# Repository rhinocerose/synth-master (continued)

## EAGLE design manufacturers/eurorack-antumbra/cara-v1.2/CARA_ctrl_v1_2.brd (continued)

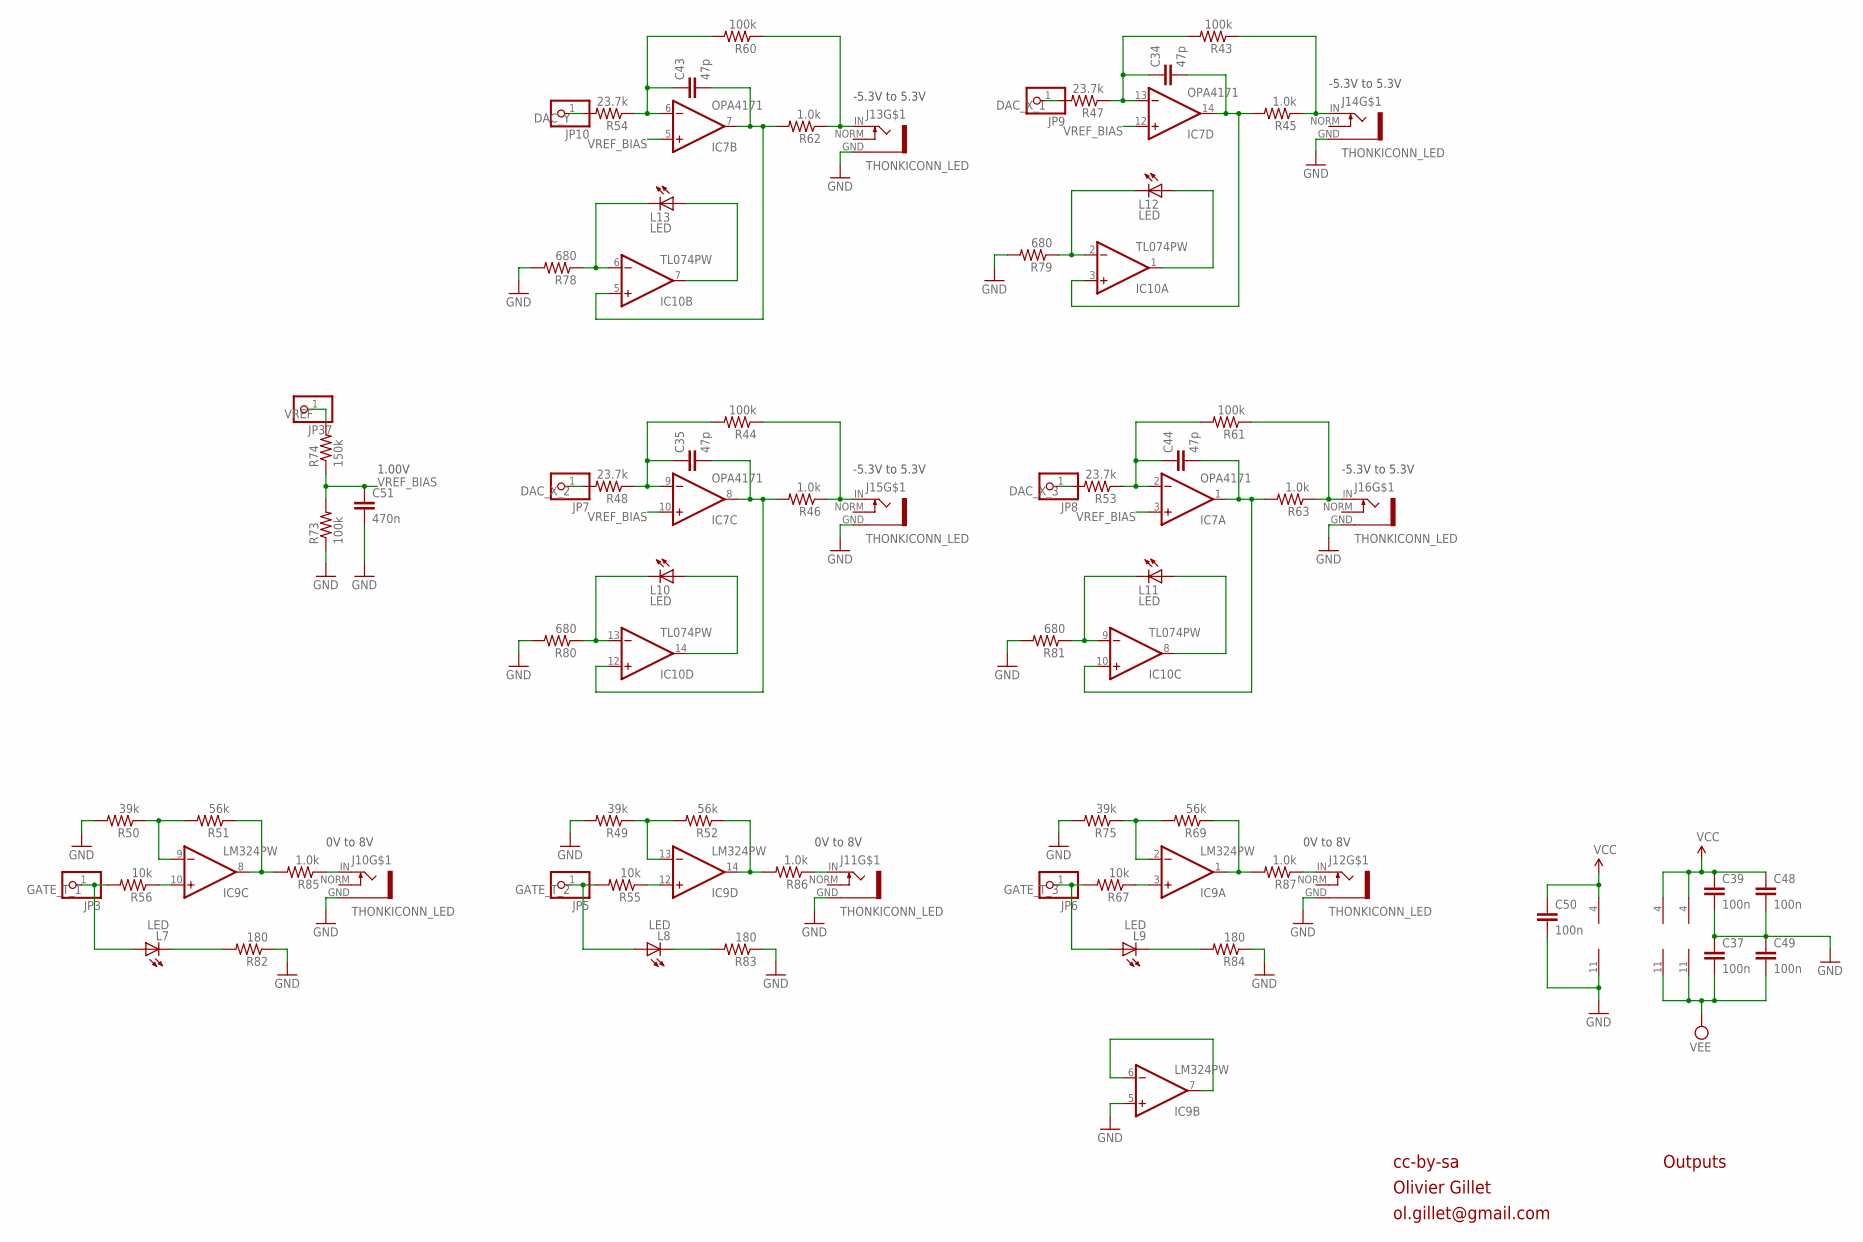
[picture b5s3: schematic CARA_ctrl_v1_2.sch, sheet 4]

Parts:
C34, C35, C43, C44: 47p; RESISTOR_0603
C37, C39, C48, C49, C50: 100n; RESISTOR_0603
C51: 470n; RESISTOR_0603
IC7: OPA4171; TSSOP14_065
IC9: LM324PW; TSSOP14_065
IC10: TL074PW; TSSOP14_065
J10, J11, J12, J13, J14, J15, J16: THONKICONN_LED; LED_JACK
JP3, JP5, JP6, JP7, JP8, JP9, JP10, JP37: PINHD-1X1; 1X01
L7, L8, L9, L10, L11, L12, L13: LED; LED_3MM
R43, R44, R60, R61, R73: 100k; RESISTOR_0603
R45, R46, R62, R63, R85, R86, R87: 1.0k; RESISTOR_0603
R47, R48, R53, R54: 23.7k; RESISTOR_0603
R49, R50, R75: 39k; RESISTOR_0603
R51, R52, R69: 56k; RESISTOR_0603
R55, R56, R67: 10k; RESISTOR_0603
R74: 150k; RESISTOR_0603
R78, R79, R80, R81: 680; RESISTOR_0603
R82, R83, R84: 180; RESISTOR_0603

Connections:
DAC_X_1: JP9.1, R47.2
DAC_X_2: JP7.1, R48.2
DAC_X_3: JP8.1, R53.2
DAC_Y: JP10.1, R54.2
GATE_T_1: JP3.1, L7.A, R56.2
GATE_T_2: JP5.1, L8.A, R55.2
GATE_T_3: JP6.1, L9.A, R67.2
GND: C37.1, C39.2, C48.2, C49.1, C50.2, C51.2, IC9.5 (+IN), IC9.11 (V-), J10.GND, J11.GND, J12.GND, J13.GND, J14.GND, J15.GND, J16.GND, R49.2, R50.2, R73.1, R75.2, R78.2, R79.2, R80.2, R81.2, R82.1, R83.1, R84.1; also elsewhere on the board
unnamed: IC9.12 (+IN), R55.1
unnamed: IC9.8 (OUT), R51.1, R85.2
unnamed: J10.IN, R85.1
unnamed: IC9.9 (-IN), R50.1, R51.2
unnamed: L7.K (C), R82.2
unnamed: IC9.10 (+IN), R56.1
unnamed: IC9.6 (-IN), IC9.7 (OUT)
unnamed: IC9.14 (OUT), R52.1, R86.2
unnamed: IC9.13 (-IN), R49.1, R52.2
unnamed: IC9.3 (+IN), R67.1
unnamed: IC9.1 (OUT), R69.1, R87.2
unnamed: J11.IN, R86.1
unnamed: J12.IN, R87.1
unnamed: IC9.2 (-IN), R69.2, R75.1
unnamed: L8.K (C), R83.2
unnamed: C43.2, IC7.7 (OUT), IC10.5 (+IN), R62.2
unnamed: L9.K (C), R84.2
unnamed: J15.IN, R44.1, R46.1
unnamed: J13.IN, R60.1, R62.1
unnamed: C35.1, IC7.9 (-IN), R44.2, R48.1
unnamed: J16.IN, R61.1, R63.1
unnamed: C44.1, IC7.2 (-IN), R53.1, R61.2
unnamed: C34.1, IC7.13 (-IN), R43.2, R47.1
unnamed: C43.1, IC7.6 (-IN), R54.1, R60.2
unnamed: J14.IN, R43.1, R45.1
unnamed: IC10.6 (-IN), L13.K (C), R78.1
unnamed: IC10.7 (OUT), L13.A
unnamed: C34.2, IC7.14 (OUT), IC10.3 (+IN), R45.2
unnamed: IC10.2 (-IN), L12.K (C), R79.1
unnamed: IC10.1 (OUT), L12.A
unnamed: C35.2, IC7.8 (OUT), IC10.12 (+IN), R46.2
unnamed: IC10.13 (-IN), L10.K (C), R80.1
unnamed: IC10.14 (OUT), L10.A
unnamed: C44.2, IC7.1 (OUT), IC10.10 (+IN), R63.2
unnamed: IC10.9 (-IN), L11.K (C), R81.1
unnamed: IC10.8 (OUT), L11.A
VCC: C39.1, C48.1, C50.1, IC7.4 (V+), IC9.4 (V+), IC10.4 (V+); also elsewhere on the board
VEE: C37.2, C49.2, IC7.11 (V-), IC10.11 (V-); also elsewhere on the board
VREF: JP37.1, R74.2
VREF_BIAS: C51.1, IC7.3 (+IN), IC7.5 (+IN), IC7.10 (+IN), IC7.12 (+IN), R73.2, R74.1

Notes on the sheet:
-5.3V to 5.3V
0V to 8V
cc-by-sa
Olivier Gillet
ol.gillet@gmail.com
Outputs
1.00V

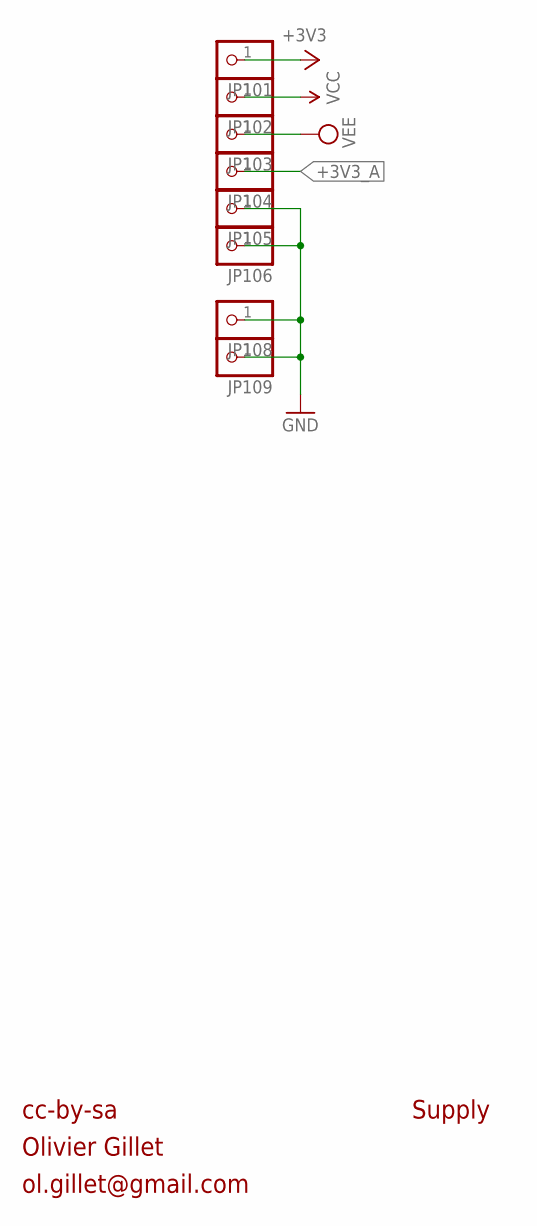
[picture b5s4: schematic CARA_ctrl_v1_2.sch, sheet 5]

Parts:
JP101, JP102, JP103, JP104, JP105, JP106, JP108, JP109: PINHD-1X1; 1X01

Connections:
+3V3: JP101.1; also elsewhere on the board
+3V3_A: JP104.1; also elsewhere on the board
GND: JP105.1, JP106.1, JP108.1, JP109.1; also elsewhere on the board
VCC: JP102.1; also elsewhere on the board
VEE: JP103.1; also elsewhere on the board

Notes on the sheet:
cc-by-sa
Olivier Gillet
ol.gillet@gmail.com
Supply

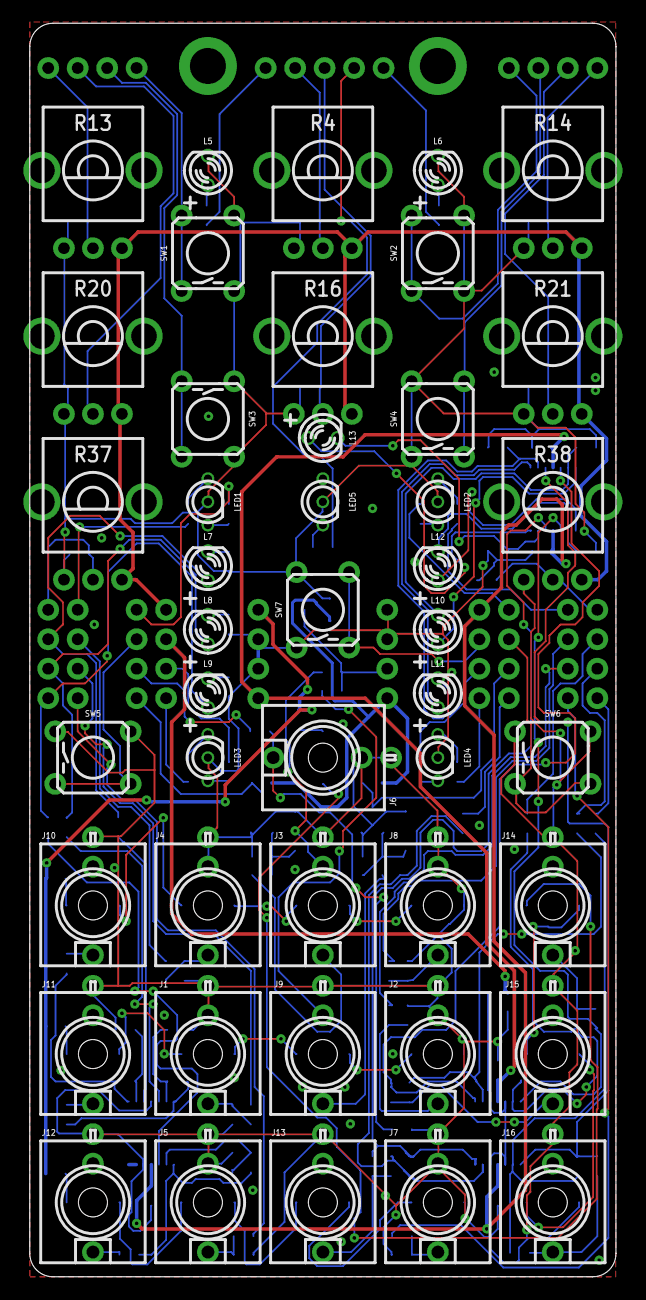
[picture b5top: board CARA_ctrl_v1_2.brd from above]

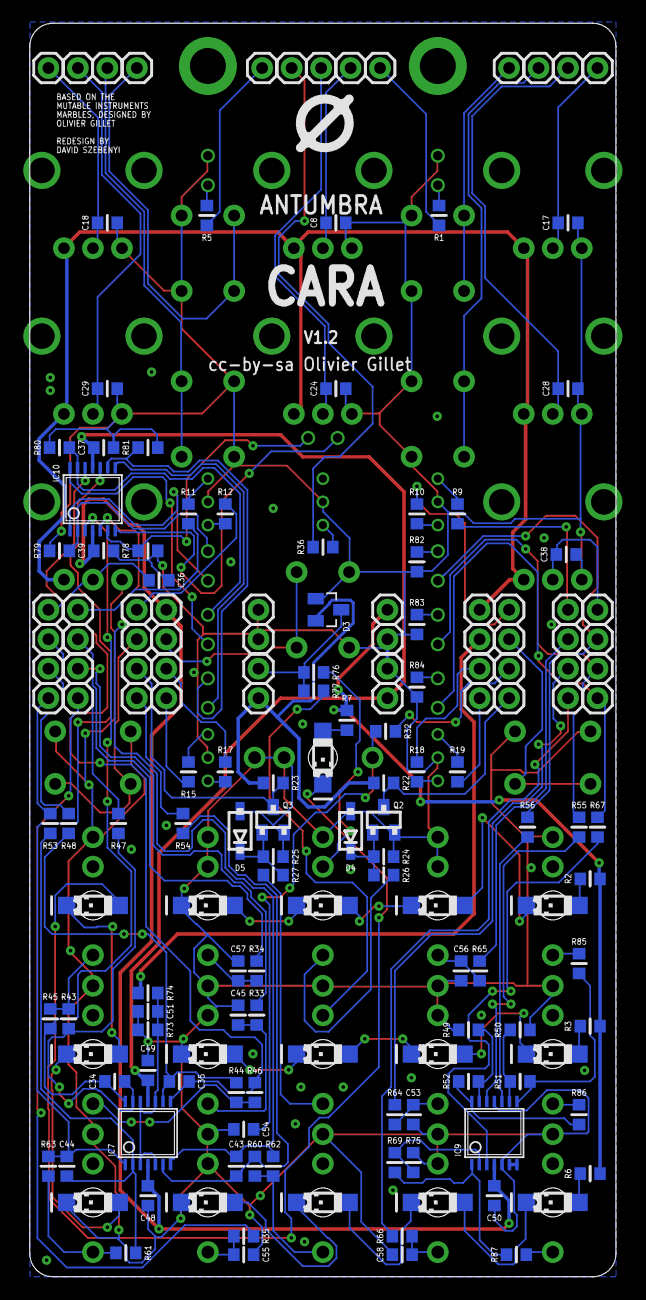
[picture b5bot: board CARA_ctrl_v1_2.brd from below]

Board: 2 copper layers, 50.5 x 108.0 mm, 197 parts (150 on the bottom side), 127 nets.

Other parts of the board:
U$1: LOGO_5

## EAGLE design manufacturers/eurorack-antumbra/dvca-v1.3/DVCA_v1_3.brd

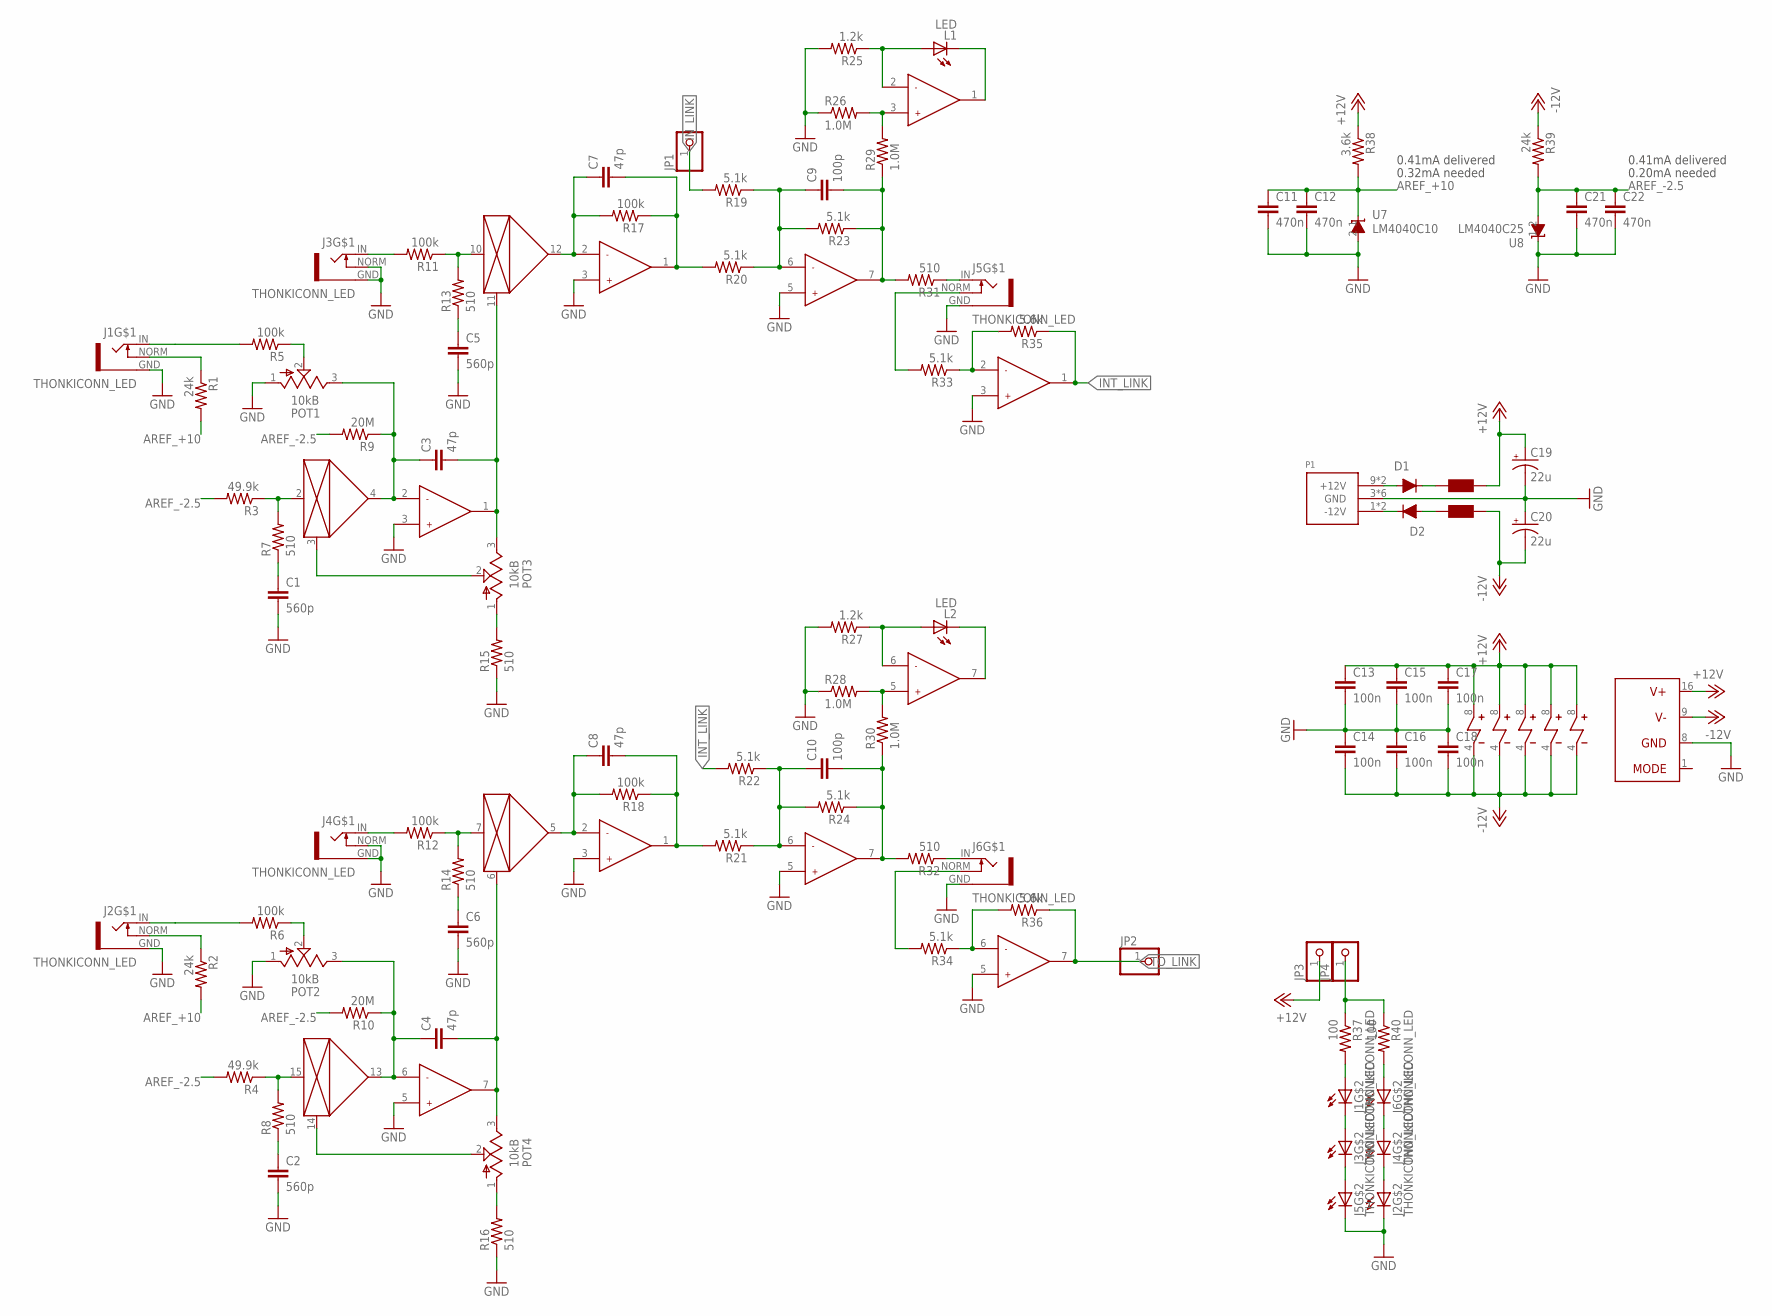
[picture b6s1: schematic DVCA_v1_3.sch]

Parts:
C1, C2, C5, C6: 560p; RESISTOR_0603
C3, C4, C7, C8: 47p; RESISTOR_0603
C9, C10: 100p; RESISTOR_0603
C11, C12, C21, C22: 470n; RESISTOR_0603
C13, C14, C15, C16, C17, C18: 100n; RESISTOR_0603
C19, C20: 22u; PANASONIC_B
D1, D2: 1N5819HW; SOD123
F1, F2: FERRITE-BEAD; RESISTOR_0603
J1, J2, J3, J4, J5, J6: THONKICONN_LED; LED_JACK
JP1, JP2, JP3, JP4: PINHD-1X1; 1X01
L1, L2: LED; LED_3MM
P1: POWER_SIMPLE10; POWER_10
POT1, POT2: 10kB; ALPS_POT_VERTICAL
POT3, POT4: 10kB; ALPS_POT_NOHOLE
R1, R2, R39: 24k; RESISTOR_0603
R3, R4: 49.9k; RESISTOR_0603
R5, R6, R11, R12, R17, R18: 100k; RESISTOR_0603
R7, R8, R13, R14, R15, R16, R31, R32: 510; RESISTOR_0603
R9, R10: 20M; RESISTOR_0603
R19, R20, R21, R22, R23, R24, R33, R34: 5.1k; RESISTOR_0603
R25, R27: 1.2k; RESISTOR_0603
R26, R28, R29, R30: 1.0M; RESISTOR_0603
R35, R36: 5.6k; RESISTOR_0603
R37, R40: 100; RESISTOR_0603
R38: 3.6k; RESISTOR_0603
U1: V2164M; SOIC16
U2, U3, U4, U5, U6: OPAMP_DUAL; SOIC8
U7: LM4040C10; SOT23
U8: LM4040C25; SOT23

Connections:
+12V: C13.1, C15.1, C17.1, C19.+, F1.1, JP3.1, R38.1, U1.16, U2.8, U3.8, U4.8, U5.8, U6.8
-12V: C14.2, C16.2, C18.2, C20.-, F2.1, R39.1, U1.9, U2.4, U3.4, U4.4, U5.4, U6.4
AREF_+10: C11.1, C12.1, R1.2, R2.2, R38.2, U7.1 (C)
AREF_-2.5: C21.1, C22.1, R3.2, R4.2, R9.2, R10.2, R39.2, U8.2 (A)
CV_IN_1: J1.IN, R5.2
FOO: R3.1, R7.2, U1.2
FOO1: R4.1, R8.2, U1.15
GND: C1.2, C2.2, C5.2, C6.2, C11.2, C12.2, C13.2, C14.1, C15.2, C16.1, C17.2, C18.1, C19.-, C20.+, C21.2, C22.2, J1.GND, J2.C, J2.GND, J3.GND, J3.NORM, J4.GND, J4.NORM, J5.C, J5.GND, J6.GND, P1.3 (GND), P1.4 (GND), P1.5 (GND), P1.6 (GND), P1.7 (GND), P1.8 (GND), POT1.1 (A), POT2.1 (A), R15.1, R16.1, R25.2, R26.1, R27.2, R28.1, U1.8, U2.3, U2.5, U3.3, U3.5, U4.3, U4.5, U6.3, U6.5, U7.2 (A), U8.1 (C)
INT_LINK: R22.2, R35.1, U6.1
IN_LINK: JP1.1, R19.2
unnamed: R26.2, R29.2, U5.3
unnamed: D1.+, P1.9 (+12V), P1.10 (+12V)
unnamed: J4.IN, R12.2
unnamed: R28.2, R30.2, U5.5
unnamed: D2.-, P1.1 (-12V), P1.2 (-12V)
unnamed: J6.IN, R32.1
unnamed: J5.IN, R31.1
unnamed: D1.-, F1.2
unnamed: POT3.2 (W), U1.3
unnamed: C9.1, R19.1, R20.1, R23.2, U3.6
unnamed: J2.A, J4.C
unnamed: JP4.1, R37.1, R40.1
unnamed: J4.A, J6.C
unnamed: POT1.2 (W), R5.1
unnamed: POT3.1 (A), R15.2
unnamed: C6.1, R14.1
unnamed: L1.K (C), U5.1
unnamed: L1.A, R25.1, U5.2
unnamed: C1.1, R7.1
unnamed: J1.NORM, R1.1
unnamed: R33.1, R35.2, U6.2
unnamed: D2.+, F2.2
unnamed: R12.1, R14.2, U1.7
unnamed: J5.NORM, R33.2
unnamed: POT4.2 (W), U1.14
unnamed: C10.1, R21.1, R22.1, R24.2, U4.6
unnamed: J6.A, R40.2
unnamed: J3.C, J5.A
unnamed: J1.C, J3.A
unnamed: J1.A, R37.2
unnamed: POT4.1 (A), R16.2
unnamed: C4.2, POT4.3 (B), U1.6, U2.7
unnamed: C4.1, POT2.3 (B), R10.1, U1.13, U2.6
unnamed: L2.K (C), U5.7
unnamed: L2.A, R27.1, U5.6
unnamed: R34.1, R36.2, U6.6
unnamed: J6.NORM, R34.2
unnamed: C8.2, R18.1, R21.2, U4.1
unnamed: POT2.2 (W), R6.1
unnamed: C2.1, R8.1
unnamed: C3.1, POT1.3 (B), R9.1, U1.4, U2.2
unnamed: J2.IN, R6.2
unnamed: C5.1, R13.1
unnamed: C8.1, R18.2, U1.5, U4.2
unnamed: J2.NORM, R2.1
unnamed: J3.IN, R11.2
unnamed: R11.1, R13.2, U1.10
unnamed: C3.2, POT3.3 (B), U1.11, U2.1
unnamed: C7.1, R17.2, U1.12, U3.2
unnamed: C7.2, R17.1, R20.2, U3.1
OUT1: C9.2, R23.1, R29.1, R31.2, U3.7
OUT2: C10.2, R24.1, R30.1, R32.2, U4.7
TO_LINK: JP2.1, R36.1, U6.7

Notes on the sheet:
0.41mA delivered
0.20mA needed
0.32mA needed

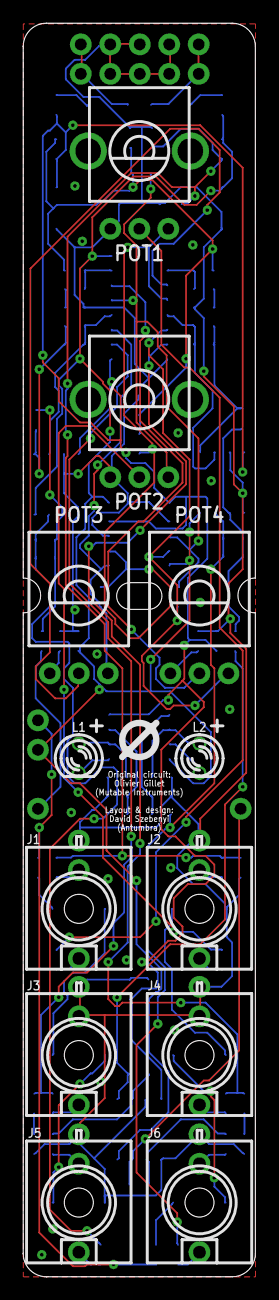
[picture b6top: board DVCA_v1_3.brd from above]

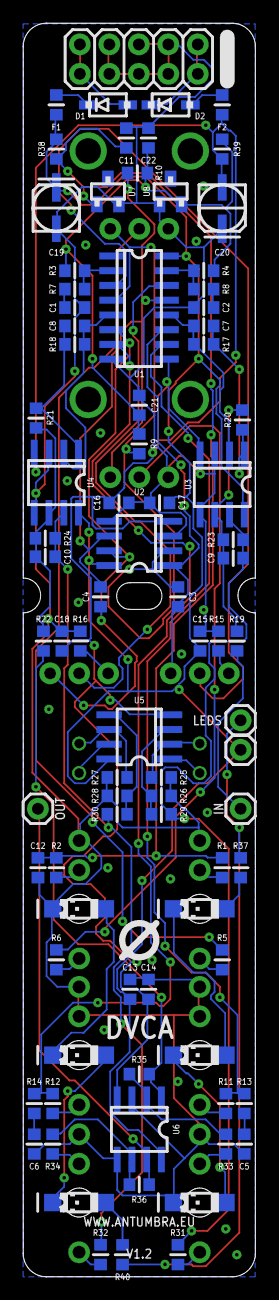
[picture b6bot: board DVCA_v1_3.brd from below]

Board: 2 copper layers, 20.0 x 108.0 mm, 93 parts (80 on the bottom side), 63 nets.

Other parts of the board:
U$1, U$2: LOGO_3.5

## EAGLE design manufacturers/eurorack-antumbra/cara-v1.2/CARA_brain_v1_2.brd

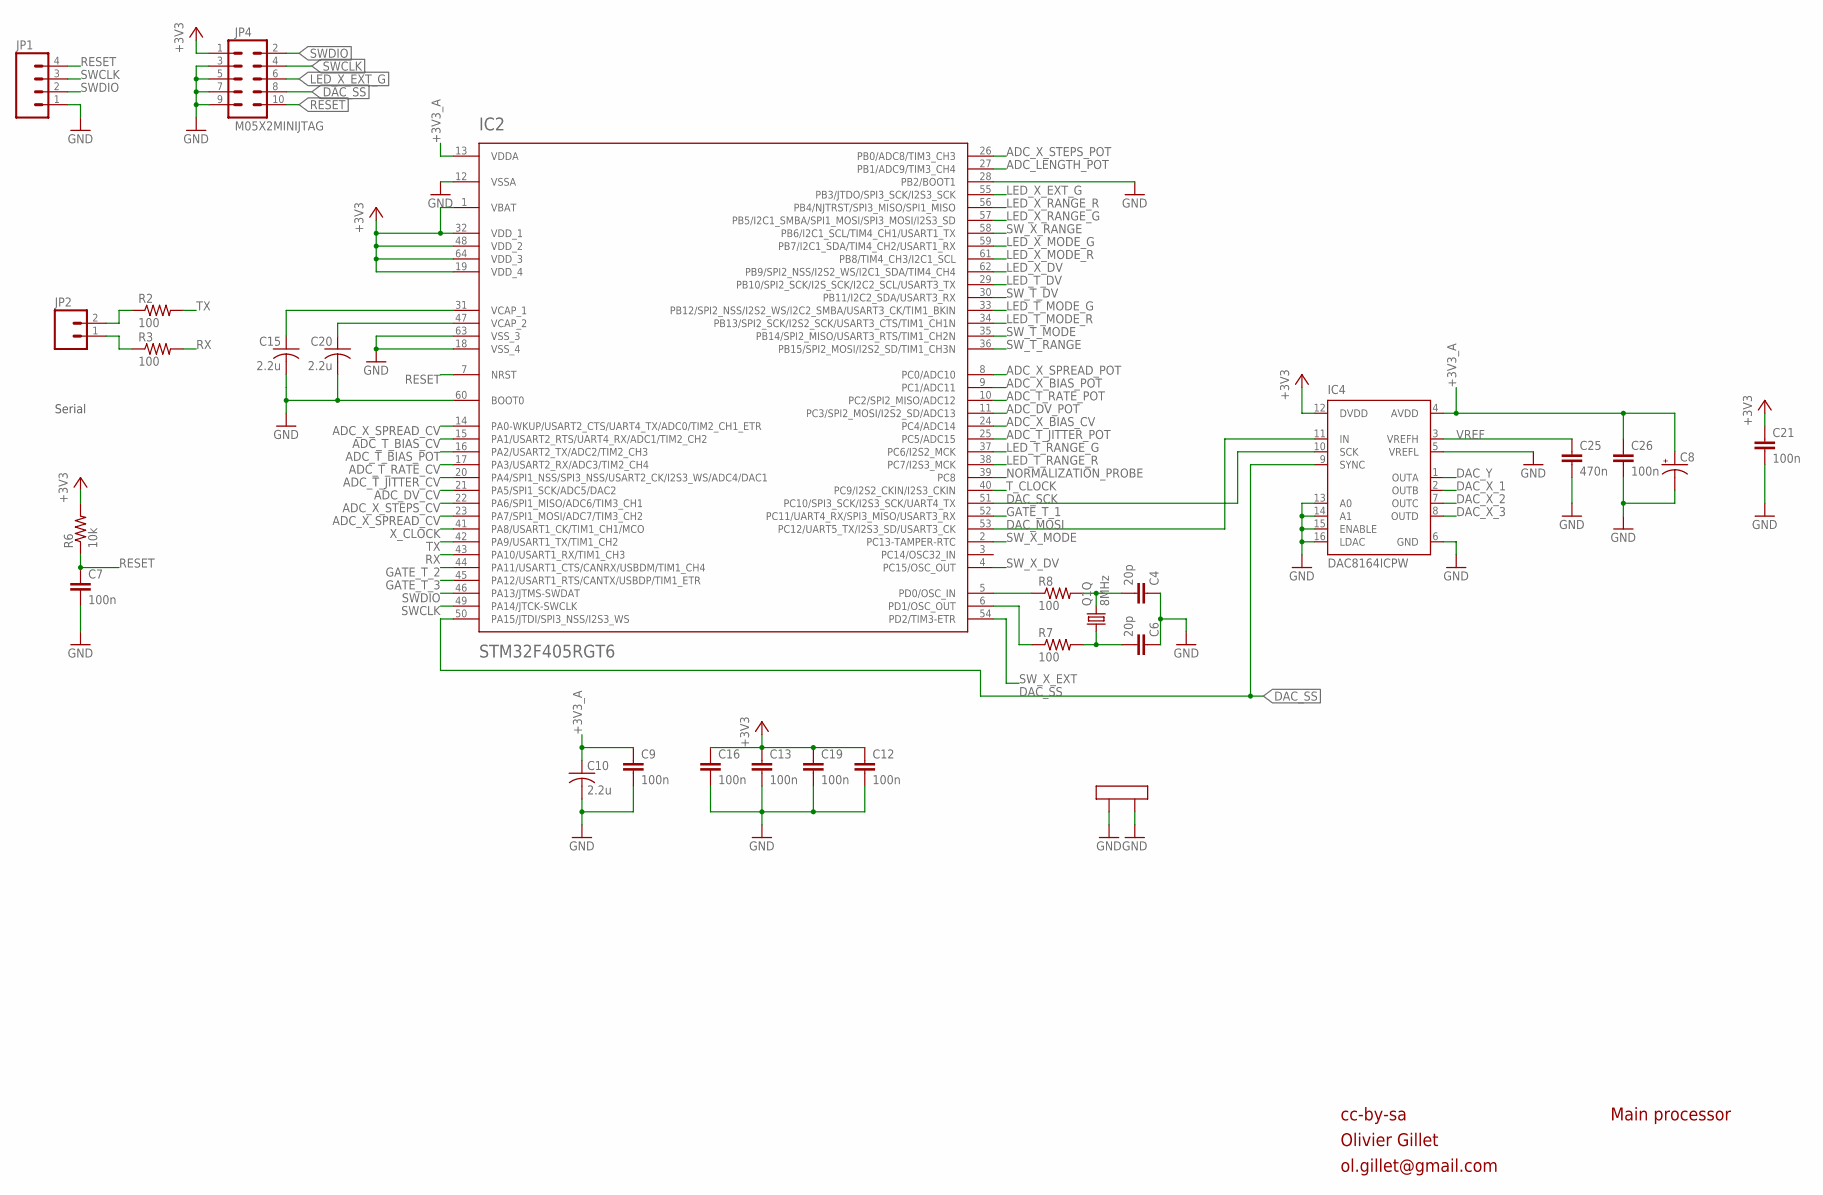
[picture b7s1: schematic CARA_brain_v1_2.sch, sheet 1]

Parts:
C4, C6: 20p; RESISTOR_0603
C7, C9, C12, C13, C16, C19, C21, C26: 100n; RESISTOR_0603
C8: CAP_POLC; PANASONIC_C
C10, C15, C20: 2.2u; C0805
C25: 470n; RESISTOR_0603
IC2: STM32F405RGT6; TQFP-10X10-64
IC4: DAC8164ICPW; SOP65P640X110-16N
JP1: M04PTH; 1X04
JP2: M02PTH; 1X02
JP4: M05X2MINIJTAG; 2X5-1.27
Q1: 8MHz; CTS406
R2, R3, R7, R8: 100; RESISTOR_0603
R6: 10k; RESISTOR_0603

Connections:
+3V3: C12.1, C13.1, C16.1, C19.1, C21.1, IC2.1 (VBAT), IC2.19 (VDD_4), IC2.32 (VDD_1), IC2.48 (VDD_2), IC2.64 (VDD_3), IC4.12 (DVDD), JP4.1, R6.2; also elsewhere on the board
+3V3_A: C8.+, C9.1, C10.1, C26.1, IC2.13 (VDDA), IC4.4 (AVDD); also elsewhere on the board
ADC_DV_CV: IC2.21 (PA5/SPI1_SCK/ADC5/DAC2); also elsewhere on the board
ADC_DV_POT: IC2.11 (PC3/SPI2_MOSI/I2S2_SD/ADC13); also elsewhere on the board
ADC_LENGTH_POT: IC2.27 (PB1/ADC9/TIM3_CH4); also elsewhere on the board
ADC_T_BIAS_CV: IC2.15 (PA1/USART2_RTS/UART4_RX/ADC1/TIM2_CH2); also elsewhere on the board
ADC_T_BIAS_POT: IC2.16 (PA2/USART2_TX/ADC2/TIM2_CH3); also elsewhere on the board
ADC_T_JITTER_CV: IC2.20 (PA4/SPI1_NSS/SPI3_NSS/USART2_CK/I2S3_WS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); also elsewhere on the board
ADC_T_JITTER_POT: IC2.25 (PC5/ADC15); also elsewhere on the board
ADC_T_RATE_CV: IC2.17 (PA3/USART2_RX/ADC3/TIM2_CH4); also elsewhere on the board
ADC_T_RATE_POT: IC2.10 (PC2/SPI2_MISO/ADC12); also elsewhere on the board
ADC_X_BIAS_CV: IC2.24 (PC4/ADC14); also elsewhere on the board
ADC_X_BIAS_POT: IC2.9 (PC1/ADC11); also elsewhere on the board
ADC_X_SPREAD_CV: IC2.14 (PA0-WKUP/USART2_CTS/UART4_TX/ADC0/TIM2_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), IC2.23 (PA7/SPI1_MOSI/ADC7/TIM3_CH2); also elsewhere on the board
ADC_X_SPREAD_POT: IC2.8 (PC0/ADC10); also elsewhere on the board
ADC_X_STEPS_CV: IC2.22 (PA6/SPI1_MISO/ADC6/TIM3_CH1); also elsewhere on the board
ADC_X_STEPS_POT: IC2.26 (PB0/ADC8/TIM3_CH3); also elsewhere on the board
DAC_MOSI: IC2.53 (PC12/UART5_TX/I2S3_SD/USART3_CK), IC4.11 (IN)
DAC_SCK: IC2.51 (PC10/SPI3_SCK/I2S3_SCK/UART4_TX), IC4.10 (SCK)
DAC_SS: IC2.50 (PA15/JTDI/SPI3_NSS/I2S3_WS), IC4.9 (SYNC), JP4.8
DAC_X_1: IC4.2 (OUTB); also elsewhere on the board
DAC_X_2: IC4.7 (OUTC); also elsewhere on the board
DAC_X_3: IC4.8 (OUTD); also elsewhere on the board
DAC_Y: IC4.1 (OUTA); also elsewhere on the board
GATE_T_1: IC2.52 (PC11/UART4_RX/SPI3_MISO/USART3_RX); also elsewhere on the board
GATE_T_2: IC2.44 (PA11/USART1_CTS/CANRX/USBDM/TIM1_CH4); also elsewhere on the board
GATE_T_3: IC2.45 (PA12/USART1_RTS/CANTX/USBDP/TIM1_ETR); also elsewhere on the board
GND: C4.1, C6.1, C7.2, C8.-, C9.2, C10.2, C12.2, C13.2, C15.2, C16.2, C19.2, C20.2, C21.2, C25.2, C26.2, IC2.12 (VSSA), IC2.18 (VSS_4), IC2.28 (PB2/BOOT1), IC2.60 (BOOT0), IC2.63 (VSS_3), IC4.5 (VREFL), IC4.6 (GND), IC4.13 (A0), IC4.14 (A1), IC4.15 (ENABLE), IC4.16 (LDAC), JP1.1, JP4.3, JP4.5, JP4.7, JP4.9, Q1.2 (LID1), Q1.4 (LID2); also elsewhere on the board
LED_T_DV: IC2.29 (PB10/SPI2_SCK/I2S_SCK/I2C2_SCL/USART3_TX); also elsewhere on the board
LED_T_MODE_G: IC2.33 (PB12/SPI2_NSS/I2S2_WS/I2C2_SMBA/USART3_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); also elsewhere on the board
LED_T_MODE_R: IC2.34 (PB13/SPI2_SCK/I2S2_SCK/USART3_CTS/TIM1_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); also elsewhere on the board
LED_T_RANGE_G: IC2.37 (PC6/I2S2_MCK); also elsewhere on the board
LED_T_RANGE_R: IC2.38 (PC7/I2S3_MCK); also elsewhere on the board
LED_X_DV: IC2.62 (PB9/SPI2_NSS/I2S2_WS/I2C1_SDA/TIM4_CH4); also elsewhere on the board
LED_X_EXT_G: IC2.55 (PB3/JTDO/SPI3_SCK/I2S3_SCK), JP4.6; also elsewhere on the board
LED_X_MODE_G: IC2.59 (PB7/I2C1_SDA/TIM4_CH2/USART1_RX); also elsewhere on the board
LED_X_MODE_R: IC2.61 (PB8/TIM4_CH3/I2C1_SCL); also elsewhere on the board
LED_X_RANGE_G: IC2.57 (PB5/I2C1_SMBA/SPI1_MOSI/SPI3_MOSI/I2S3_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); also elsewhere on the board
LED_X_RANGE_R: IC2.56 (PB4/NJTRST/SPI3_MISO/SPI1_MISO); also elsewhere on the board
unnamed: IC2.6 (PD1/OSC_OUT), R7.1
unnamed: IC2.5 (PD0/OSC_IN), R8.1
unnamed: C20.1, IC2.47 (VCAP_2)
unnamed: C15.1, IC2.31 (VCAP_1)
unnamed: JP2.2, R2.1
unnamed: JP2.1, R3.1
unnamed: C4.2, Q1.3 (2), R8.2
unnamed: C6.2, Q1.1, R7.2
NORMALIZATION_PROBE: IC2.39 (PC8); also elsewhere on the board
RESET: C7.1, IC2.7 (NRST), JP1.4, JP4.10, R6.1
RX: IC2.43 (PA10/USART1_RX/TIM1_CH3), R3.2
SWCLK: IC2.49 (PA14/JTCK-SWCLK), JP1.3, JP4.4
SWDIO: IC2.46 (PA13/JTMS-SWDAT), JP1.2, JP4.2
SW_T_DV: IC2.30 (PB11/I2C2_SDA/USART3_RX); also elsewhere on the board
SW_T_MODE: IC2.35 (PB14/SPI2_MISO/USART3_RTS/TIM1_CH2N); also elsewhere on the board
SW_T_RANGE: IC2.36 (PB15/SPI2_MOSI/I2S2_SD/TIM1_CH3N); also elsewhere on the board
SW_X_DV: IC2.4 (PC15/OSC_OUT); also elsewhere on the board
SW_X_EXT: IC2.54 (PD2/TIM3-ETR); also elsewhere on the board
SW_X_MODE: IC2.2 (PC13-TAMPER-RTC); also elsewhere on the board
SW_X_RANGE: IC2.58 (PB6/I2C1_SCL/TIM4_CH1/USART1_TX); also elsewhere on the board
TX: IC2.42 (PA9/USART1_TX/TIM1_CH2), R2.2
T_CLOCK: IC2.40 (PC9/I2S2_CKIN/I2S3_CKIN); also elsewhere on the board
VREF: C25.1, IC4.3 (VREFH); also elsewhere on the board
X_CLOCK: IC2.41 (PA8/USART1_CK/TIM1_CH1/MCO); also elsewhere on the board

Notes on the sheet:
cc-by-sa
Olivier Gillet
ol.gillet@gmail.com
Main processor
Serial

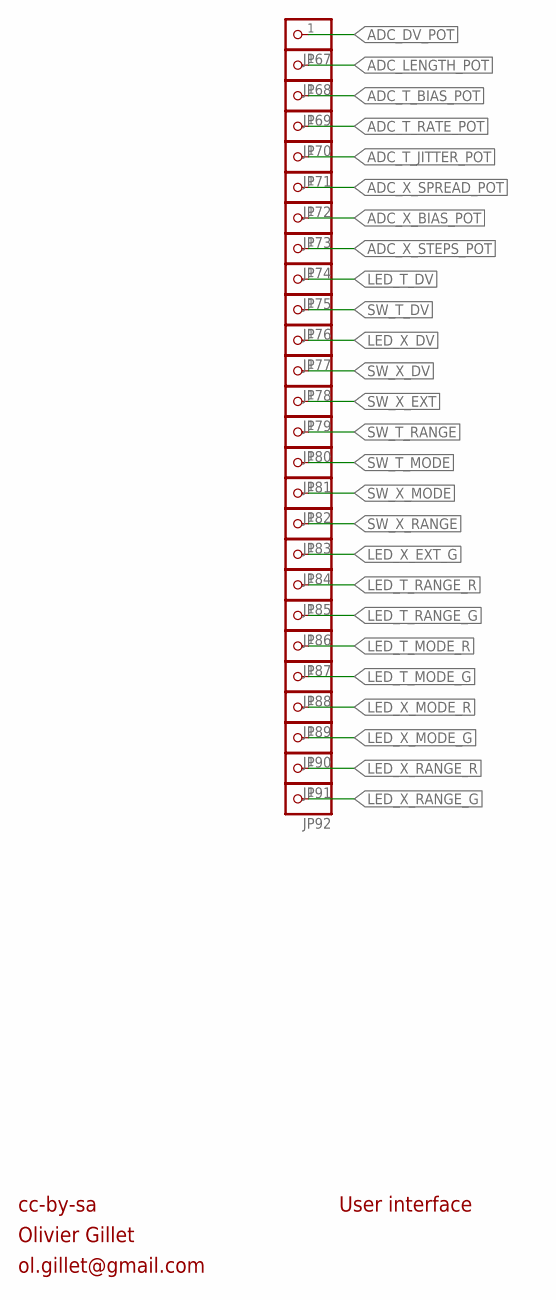
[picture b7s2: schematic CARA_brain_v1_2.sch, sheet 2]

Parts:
JP67, JP68, JP69, JP70, JP71, JP72, JP73, JP74, JP75, JP76, JP77, JP78, JP79, JP80, JP81, JP82, JP83, JP84, JP85, JP86, JP87, JP88, JP89, JP90, JP91, JP92: PINHD-1X1; 1X01

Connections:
ADC_DV_POT: JP67.1; also elsewhere on the board
ADC_LENGTH_POT: JP68.1; also elsewhere on the board
ADC_T_BIAS_POT: JP69.1; also elsewhere on the board
ADC_T_JITTER_POT: JP71.1; also elsewhere on the board
ADC_T_RATE_POT: JP70.1; also elsewhere on the board
ADC_X_BIAS_POT: JP73.1; also elsewhere on the board
ADC_X_SPREAD_POT: JP72.1; also elsewhere on the board
ADC_X_STEPS_POT: JP74.1; also elsewhere on the board
LED_T_DV: JP75.1; also elsewhere on the board
LED_T_MODE_G: JP88.1; also elsewhere on the board
LED_T_MODE_R: JP87.1; also elsewhere on the board
LED_T_RANGE_G: JP86.1; also elsewhere on the board
LED_T_RANGE_R: JP85.1; also elsewhere on the board
LED_X_DV: JP77.1; also elsewhere on the board
LED_X_EXT_G: JP84.1; also elsewhere on the board
LED_X_MODE_G: JP90.1; also elsewhere on the board
LED_X_MODE_R: JP89.1; also elsewhere on the board
LED_X_RANGE_G: JP92.1; also elsewhere on the board
LED_X_RANGE_R: JP91.1; also elsewhere on the board
SW_T_DV: JP76.1; also elsewhere on the board
SW_T_MODE: JP81.1; also elsewhere on the board
SW_T_RANGE: JP80.1; also elsewhere on the board
SW_X_DV: JP78.1; also elsewhere on the board
SW_X_EXT: JP79.1; also elsewhere on the board
SW_X_MODE: JP82.1; also elsewhere on the board
SW_X_RANGE: JP83.1; also elsewhere on the board

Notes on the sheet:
cc-by-sa
Olivier Gillet
ol.gillet@gmail.com
User interface

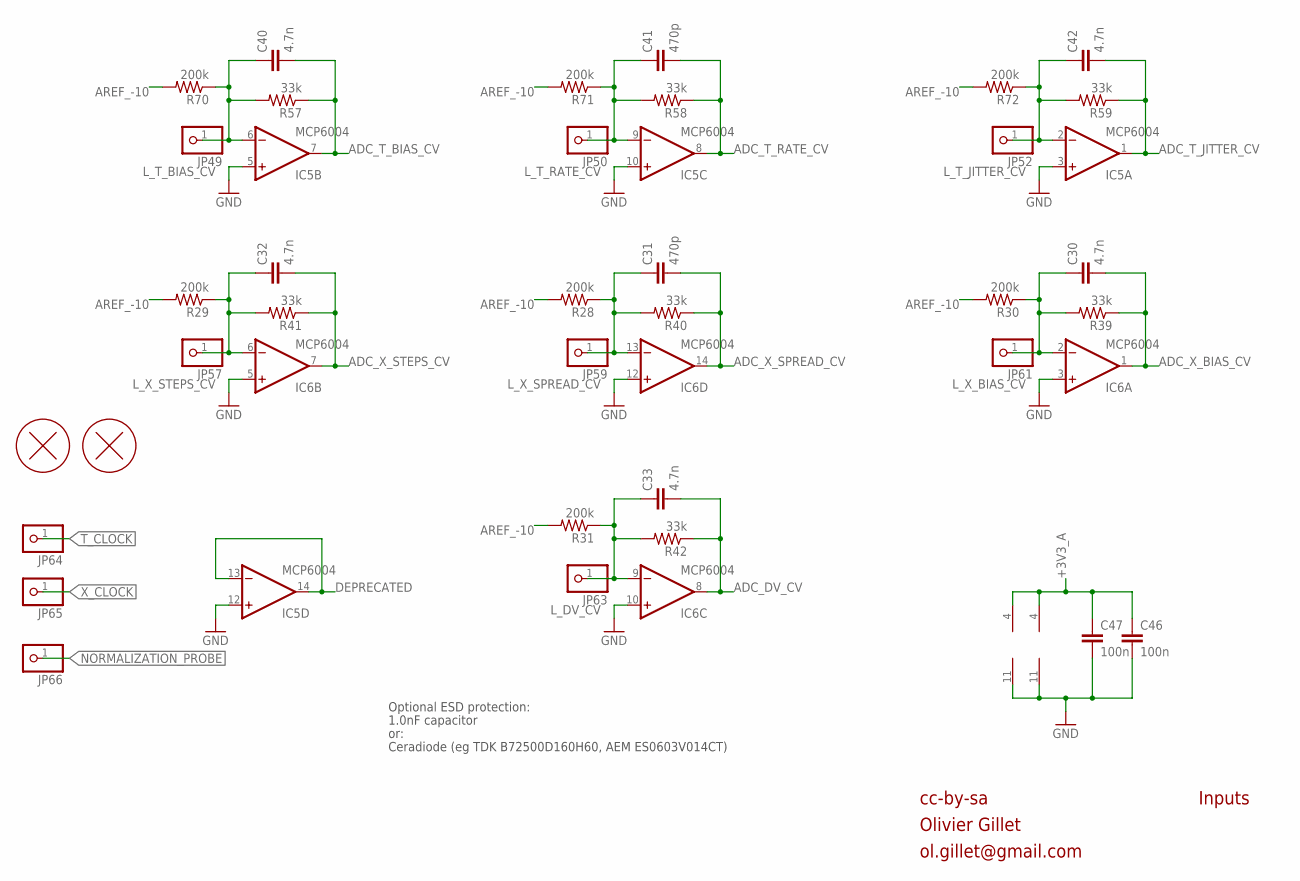
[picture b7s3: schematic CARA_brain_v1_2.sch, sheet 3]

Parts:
C30, C32, C33, C40, C42: 4.7n; RESISTOR_0603
C31, C41: 470p; RESISTOR_0603
C46, C47: 100n; RESISTOR_0603
H1, H2: PCB_SCREW
IC5, IC6: MCP6004; TSSOP14_065
JP49, JP50, JP52, JP57, JP59, JP61, JP63, JP64, JP65, JP66: PINHD-1X1; 1X01
R28, R29, R30, R31, R70, R71, R72: 200k; RESISTOR_0603
R39, R40, R41, R42, R57, R58, R59: 33k; RESISTOR_0603

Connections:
+3V3_A: C46.1, C47.1, IC5.4 (V+), IC6.4 (V+); also elsewhere on the board
ADC_DV_CV: C33.2, IC6.8 (OUT), R42.1; also elsewhere on the board
ADC_T_BIAS_CV: C40.2, IC5.7 (OUT), R57.1; also elsewhere on the board
ADC_T_JITTER_CV: C42.2, IC5.1 (OUT), R59.1; also elsewhere on the board
ADC_T_RATE_CV: C41.2, IC5.8 (OUT), R58.1; also elsewhere on the board
ADC_X_BIAS_CV: C30.2, IC6.1 (OUT), R39.1; also elsewhere on the board
ADC_X_SPREAD_CV: C31.2, IC6.14 (OUT), R40.1; also elsewhere on the board
ADC_X_STEPS_CV: C32.2, IC6.7 (OUT), R41.1; also elsewhere on the board
AREF_-10: R28.2, R29.2, R30.2, R31.2, R70.2, R71.2, R72.2; also elsewhere on the board
DEPRECATED: IC5.13 (-IN), IC5.14 (OUT)
GND: C46.2, C47.2, IC5.3 (+IN), IC5.5 (+IN), IC5.10 (+IN), IC5.11 (V-), IC5.12 (+IN), IC6.3 (+IN), IC6.5 (+IN), IC6.10 (+IN), IC6.11 (V-), IC6.12 (+IN); also elsewhere on the board
L_DV_CV: C33.1, IC6.9 (-IN), JP63.1, R31.1, R42.2
L_T_BIAS_CV: C40.1, IC5.6 (-IN), JP49.1, R57.2, R70.1
L_T_JITTER_CV: C42.1, IC5.2 (-IN), JP52.1, R59.2, R72.1
L_T_RATE_CV: C41.1, IC5.9 (-IN), JP50.1, R58.2, R71.1
L_X_BIAS_CV: C30.1, IC6.2 (-IN), JP61.1, R30.1, R39.2
L_X_SPREAD_CV: C31.1, IC6.13 (-IN), JP59.1, R28.1, R40.2
L_X_STEPS_CV: C32.1, IC6.6 (-IN), JP57.1, R29.1, R41.2
NORMALIZATION_PROBE: JP66.1; also elsewhere on the board
T_CLOCK: JP64.1; also elsewhere on the board
X_CLOCK: JP65.1; also elsewhere on the board

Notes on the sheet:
cc-by-sa
Olivier Gillet
ol.gillet@gmail.com
Inputs
Optional ESD protection:
1.0nF capacitor
or:
Ceradiode (eg TDK B72500D160H60, AEM ES0603V014CT)
